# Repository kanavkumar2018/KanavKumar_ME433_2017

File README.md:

# KanavKumar_ME433_2017
# ME433_2017

Course website for Advanced Mechatronics at NU in Spring 2017

All information is on the git wiki! https://github.com/ndm736/ME433_2017/wiki

Kanav Kumar
03/22/17

Repository Contents:
PIC32 Circuit Diagram
HW1 (NScope of Voltage Regulator)
Photo of Breadboard

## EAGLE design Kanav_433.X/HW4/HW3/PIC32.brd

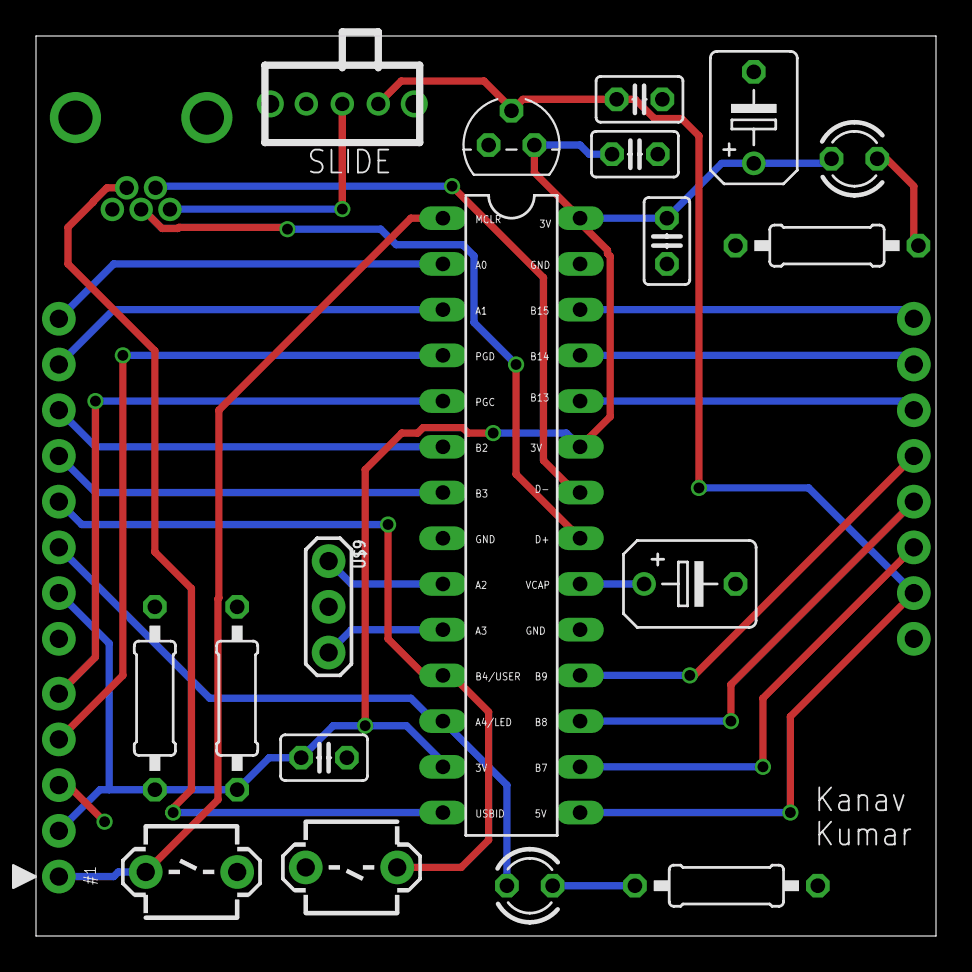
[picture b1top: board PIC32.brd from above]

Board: 2 copper layers, 50.0 x 50.0 mm, 22 parts (0 on the bottom side), 27 nets.

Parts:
C1, C2, C3, C4: .1uF; C025-025X050
C5, C6: 10uF; B45181B
J1: USB-MB-H
LED1: RED; LED3MM
LED2: GREEN; LED3MM
R1, R2: 330; 0207/10
R3, R4: 10k; 0207/10
U$1: PIC32MX250F128B; DIL28-3
U$2: SLIDE
U$3: MCP1702; TO92
U$4: RESET; PB
U$5: USER; PB
U$6, U$7: CONN_8; 1X08
U$8: PICKIT3; 1X05
U$9: 8MHz; OSC

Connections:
+3V3: C1.1, C2.1, C4.1, C6.+, LED1.A, R3.1, R4.1, U$1.13, U$1.23, U$1.28, U$3.3, U$7.2, U$8.2
+5V: C3.1, U$1.15, U$2.3, U$3.2, U$6.2
A0: U$1.2, U$7.8
A1: U$1.3, U$7.7
A4/LED: LED2.A, U$1.12, U$7.3
B2: U$1.6, U$7.6
B3: U$1.7, U$7.5
B4/USER: U$1.11, U$4.1, U$7.4
B7: U$1.16, U$6.3
B8: U$1.17, U$6.4
B9: U$1.18, U$6.5
B13: U$1.24, U$6.6
B14: U$1.25, U$6.7
B15: U$1.26, U$6.8
D+: J1.D+, U$1.21
D-: J1.D-, U$1.22
GND: C1.2, C2.2, C3.2, C4.2, C5.-, C6.-, R1.1, R2.1, U$1.8, U$1.19, U$1.27, U$3.1, U$4.2, U$5.2, U$6.1, U$7.1, U$8.3, U$9.2
MCLR: U$1.1, U$5.1, U$8.1
unnamed: U$1.10, U$9.3
unnamed: LED1.K, R1.2
unnamed: U$1.9, U$9.1
unnamed: C5.+, U$1.20
unnamed: LED2.K, R2.2
PGC: U$1.5, U$8.5
PGD: U$1.4, U$8.4
USBID: J1.ID, U$1.14
VBUS: J1.VBUS, U$2.2

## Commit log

2017-04-02 Create Empty
2017-04-12 ME433
2017-04-12 Consolidation
2017-04-13 Hello World Code
2017-05-06 HW5 Final
2017-05-06 Reorganizing
2017-05-06 delete
2017-05-06 HW6 Update
2017-05-06 Circuit Diagram
2017-05-08 HW12
2017-05-09 HW13
2017-05-31 HW11
2017-05-31 HW14/15
2017-05-31 HW16
2017-06-01 HW14
2017-06-02 HW 15-17
2017-06-08 Final
